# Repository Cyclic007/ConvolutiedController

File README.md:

# Convoluted Controller

This is a custom controller using Alpaca for firmware and using THB001P joysticks Made with the scheme of a nentendo controller made to not get stick drift.

This controller is built for PC gameing and not console.

The controller uses an adaFruit Fether for the microcontroller.

## Total cost $82.72

| Reference                                  | Qty | Value                | Footprint                                    | Datasheet                                                            | source                                                                                           | cost   |
|--------------------------------------------|-----|----------------------|----------------------------------------------|----------------------------------------------------------------------|--------------------------------------------------------------------------------------------------|--------|
| A2,B1,D_Down1,D_Left1,D_right1,D_UP1,X1,Y1 | 8   | Switch               | Button_Switch_SMD:SW_Push_1P1T_NO_CK_KSC6xxJ | ~                                                                    | https://www.digikey.com/en/products/detail/te-connectivity-alcoswitch-switches/1825910-6/1632536 | $1.04  |
| D1,D2,D3,D4,D9,D10,D11,D12                 | 8   | 1N4148               | Diode_THT:D_DO-35_SOD27_P7.62mm_Horizontal   | https://assets.nexperia.com/documents/data-sheet/1N4148_1N4448.pdf   | https://www.digikey.com/en/products/detail/onsemi/1N4148/458603                                  | $7.46  |
| stick1,stick2                              | 2   | THB001P              | ScottoKeebs_Miscellaneous:THB001P_CNK        | THB001P                                                              | https://www.digikey.com/en/products/detail/c-k/THB001P/11687191                                  | $5.92  |
| U1                                         | 1   | rp2040 fether | Module:Adafruit_Feather                      | https://learn.adafruit.com/introducing-the-adafruit-rp2040-feather | https://www.digikey.com/en/products/detail/adafruit-industries-llc/4884/14000603                  | $24.95 |
| PCB                                        | 1   |                      |                                              |                                                                      | https://www.pcbway.com                                                                           | $37.40 |
| Battery                                    | 1   |                      |                                              |                                                                      | https://www.adafruit.com/product/2011                                                            | $5.95  |

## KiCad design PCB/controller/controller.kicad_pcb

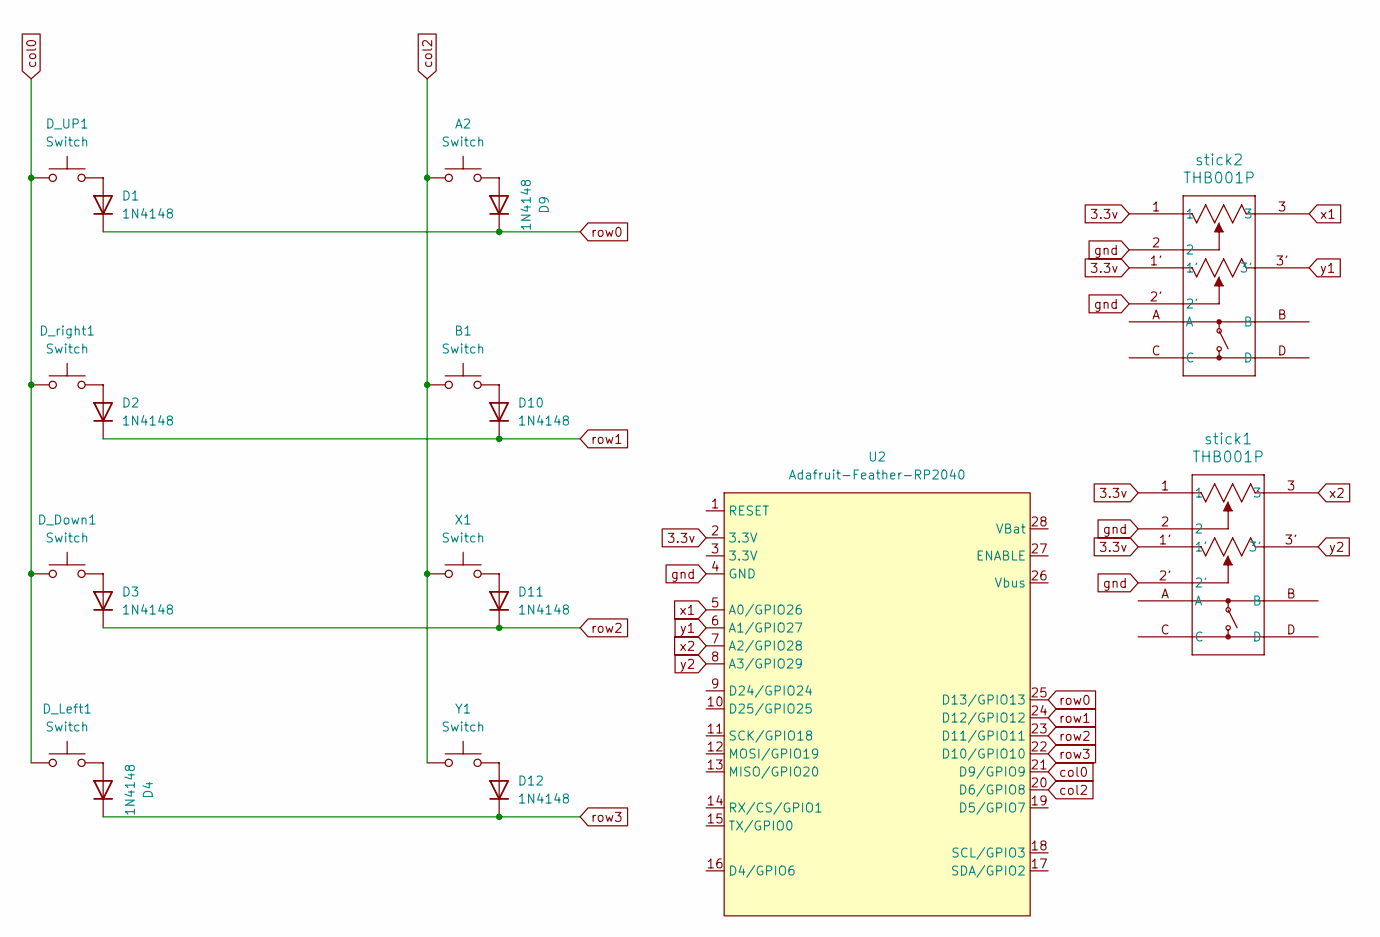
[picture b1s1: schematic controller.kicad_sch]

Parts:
A2: Switch; SW_Push_1P1T_NO_CK_KSC6xxJ
B1: Switch; SW_Push_1P1T_NO_CK_KSC6xxJ
D1, D2, D3, D4, D9, D10, D11, D12: 1N4148; D_DO-35_SOD27_P7.62mm_Horizontal
D_Down1: Switch; SW_Push_1P1T_NO_CK_KSC6xxJ
D_Left1: Switch; SW_Push_1P1T_NO_CK_KSC6xxJ
D_UP1: Switch; SW_Push_1P1T_NO_CK_KSC6xxJ
D_right1: Switch; SW_Push_1P1T_NO_CK_KSC6xxJ
U2: Adafruit-Feather-RP2040; Adafruit_Feather
X1: Switch; SW_Push_1P1T_NO_CK_KSC6xxJ
Y1: Switch; SW_Push_1P1T_NO_CK_KSC6xxJ
stick1, stick2: THB001P; THB001P_CNK

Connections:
3.3v: U2.2 (3.3V), stick1.1, stick1.1', stick2.1, stick2.1'
unnamed: D1.2 (A), D_UP1.2
unnamed: D2.2 (A), D_right1.2
unnamed: D3.2 (A), D_Down1.2
unnamed: D4.2 (A), D_Left1.2
unnamed: A2.2, D9.2 (A)
unnamed: B1.2, D10.2 (A)
unnamed: D11.2 (A), X1.2
unnamed: D12.2 (A), Y1.2
col0: D_Down1.1, D_Left1.1, D_UP1.1, D_right1.1, U2.21 (D9/GPIO9)
col2: A2.1, B1.1, U2.20 (D6/GPIO8), X1.1, Y1.1
gnd: U2.4 (GND), stick1.2, stick1.2', stick2.2, stick2.2'
row0: D1.1 (K), D9.1 (K), U2.25 (D13/GPIO13)
row1: D2.1 (K), D10.1 (K), U2.24 (D12/GPIO12)
row2: D3.1 (K), D11.1 (K), U2.23 (D11/GPIO11)
row3: D4.1 (K), D12.1 (K), U2.22 (D10/GPIO10)
x1: U2.5 (A0/GPIO26), stick2.3
x2: U2.7 (A2/GPIO28), stick1.3
y1: U2.6 (A1/GPIO27), stick2.3'
y2: U2.8 (A3/GPIO29), stick1.3'

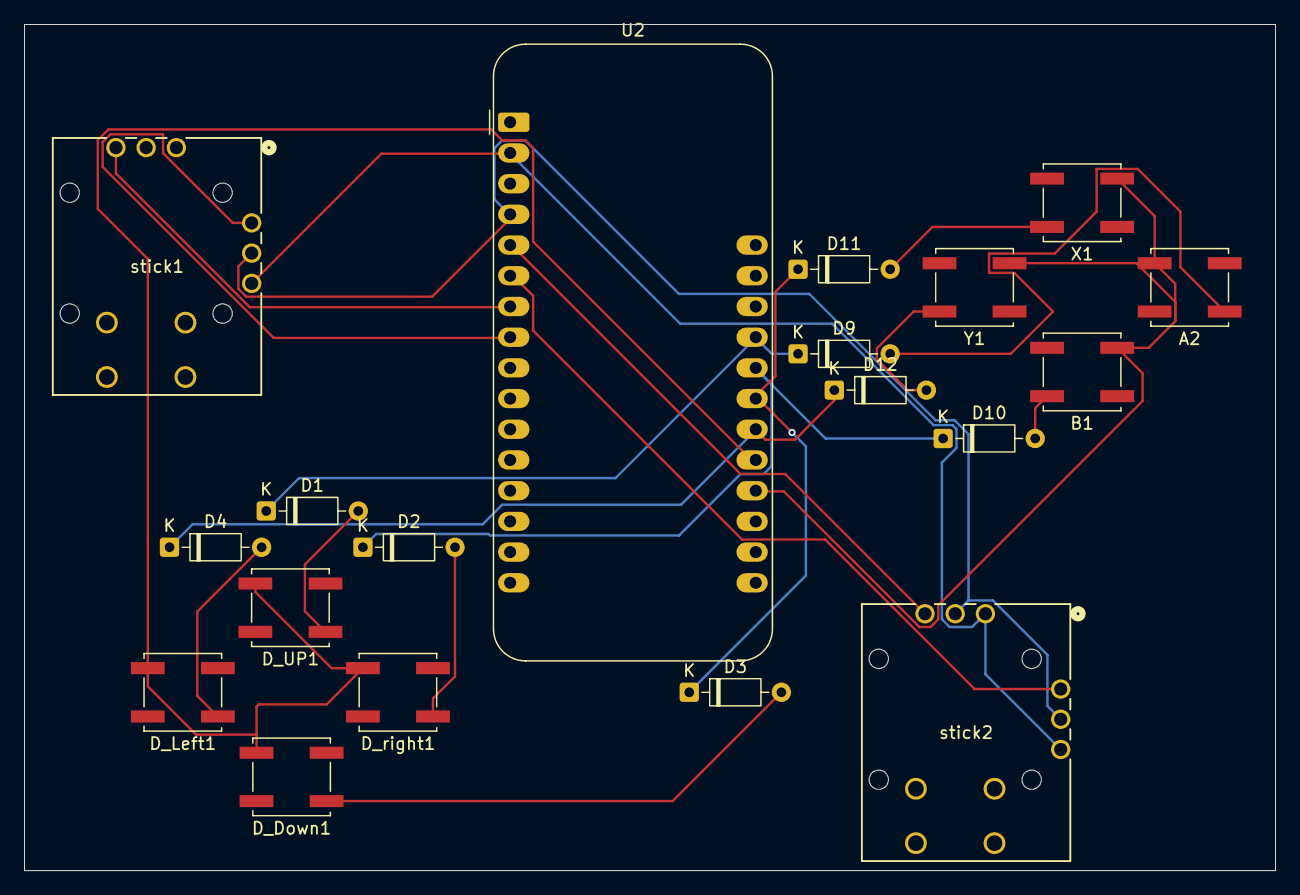
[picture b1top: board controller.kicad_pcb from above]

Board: 2 copper layers, 103.5 x 70.0 mm, 19 parts (0 on the bottom side), 20 nets.

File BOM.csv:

Reference,Qty,Value,Footprint,Datasheet,source,cost
"A2,B1,D_Down1,D_Left1,D_right1,D_UP1,X1,Y1",8,Switch,Button_Switch_SMD:SW_Push_1P1T_NO_CK_KSC6xxJ,~,https://www.digikey.com/en/products/detail/te-connectivity-a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,$1.04
"D1,D2,D3,D4,D9,D10,D11,D12",8,1N4148,Diode_THT:D_DO-35_SOD27_P7.62mm_Horizontal,https://assets.nexperia.com/documents/data-sheet/1N4148_1N4448.pdf,https://www.digikey.com/en/products/detail/onsemi/1N4148/458603,$7.46
"stick1,stick2",2,THB001P,ScottoKeebs_Miscellaneous:THB001P_CNK,THB001P,https://www.digikey.com/en/products/detail/c-k/THB001P/11687191,$5.92
U1,1,nRF52840_Featherwing,Module:Adafruit_Feather,https://learn.adafruit.com/introducing-the-adafruit-nrf52840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,https://www.digikey.com/en/products/detail/adafruit-industri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,$24.95
PCB,1,,,,https://www.pcbway.com,$37.40
Battery,1,,,,https://www.adafruit.com/product/2011,$5.95

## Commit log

2025-05-26 The Start
2025-05-27 stuff
2025-06-02 doin stuffs
2025-06-04 more work
2025-06-04 finding that I need to change micro Controller
2025-06-05 adding stuff
2025-06-05 finishing
2025-06-05 things
2025-06-05 fixing some things
2025-06-05 finding better switch
2025-06-05 fixing git ignore
2025-06-07 adding silk screen
2025-06-07 fixing things
2025-06-08 Rename controller.csv to BOM.csv
2025-06-08 firmwere
2025-06-09 Rename alpakka_pico_1_0_0.uf2 to Firmware.uf2
